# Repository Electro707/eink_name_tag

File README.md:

# E-Ink Name Tab Project, by Electro707

This project is for a E-Ink name-tag, meant to be the cooler replacement for a paper name-tag for event and shows.

## Directory

- `STM32CubeIDE`: The firmware created with STM32CubeIDE
- `PCB`: PCB Files made with KiCAD
- `PythonUploader`: A Python GUI and class to communicate with the e-ink tag, mainly to update the "frames"
- `CAD`: Mechanical enclosure made with FreeCAD

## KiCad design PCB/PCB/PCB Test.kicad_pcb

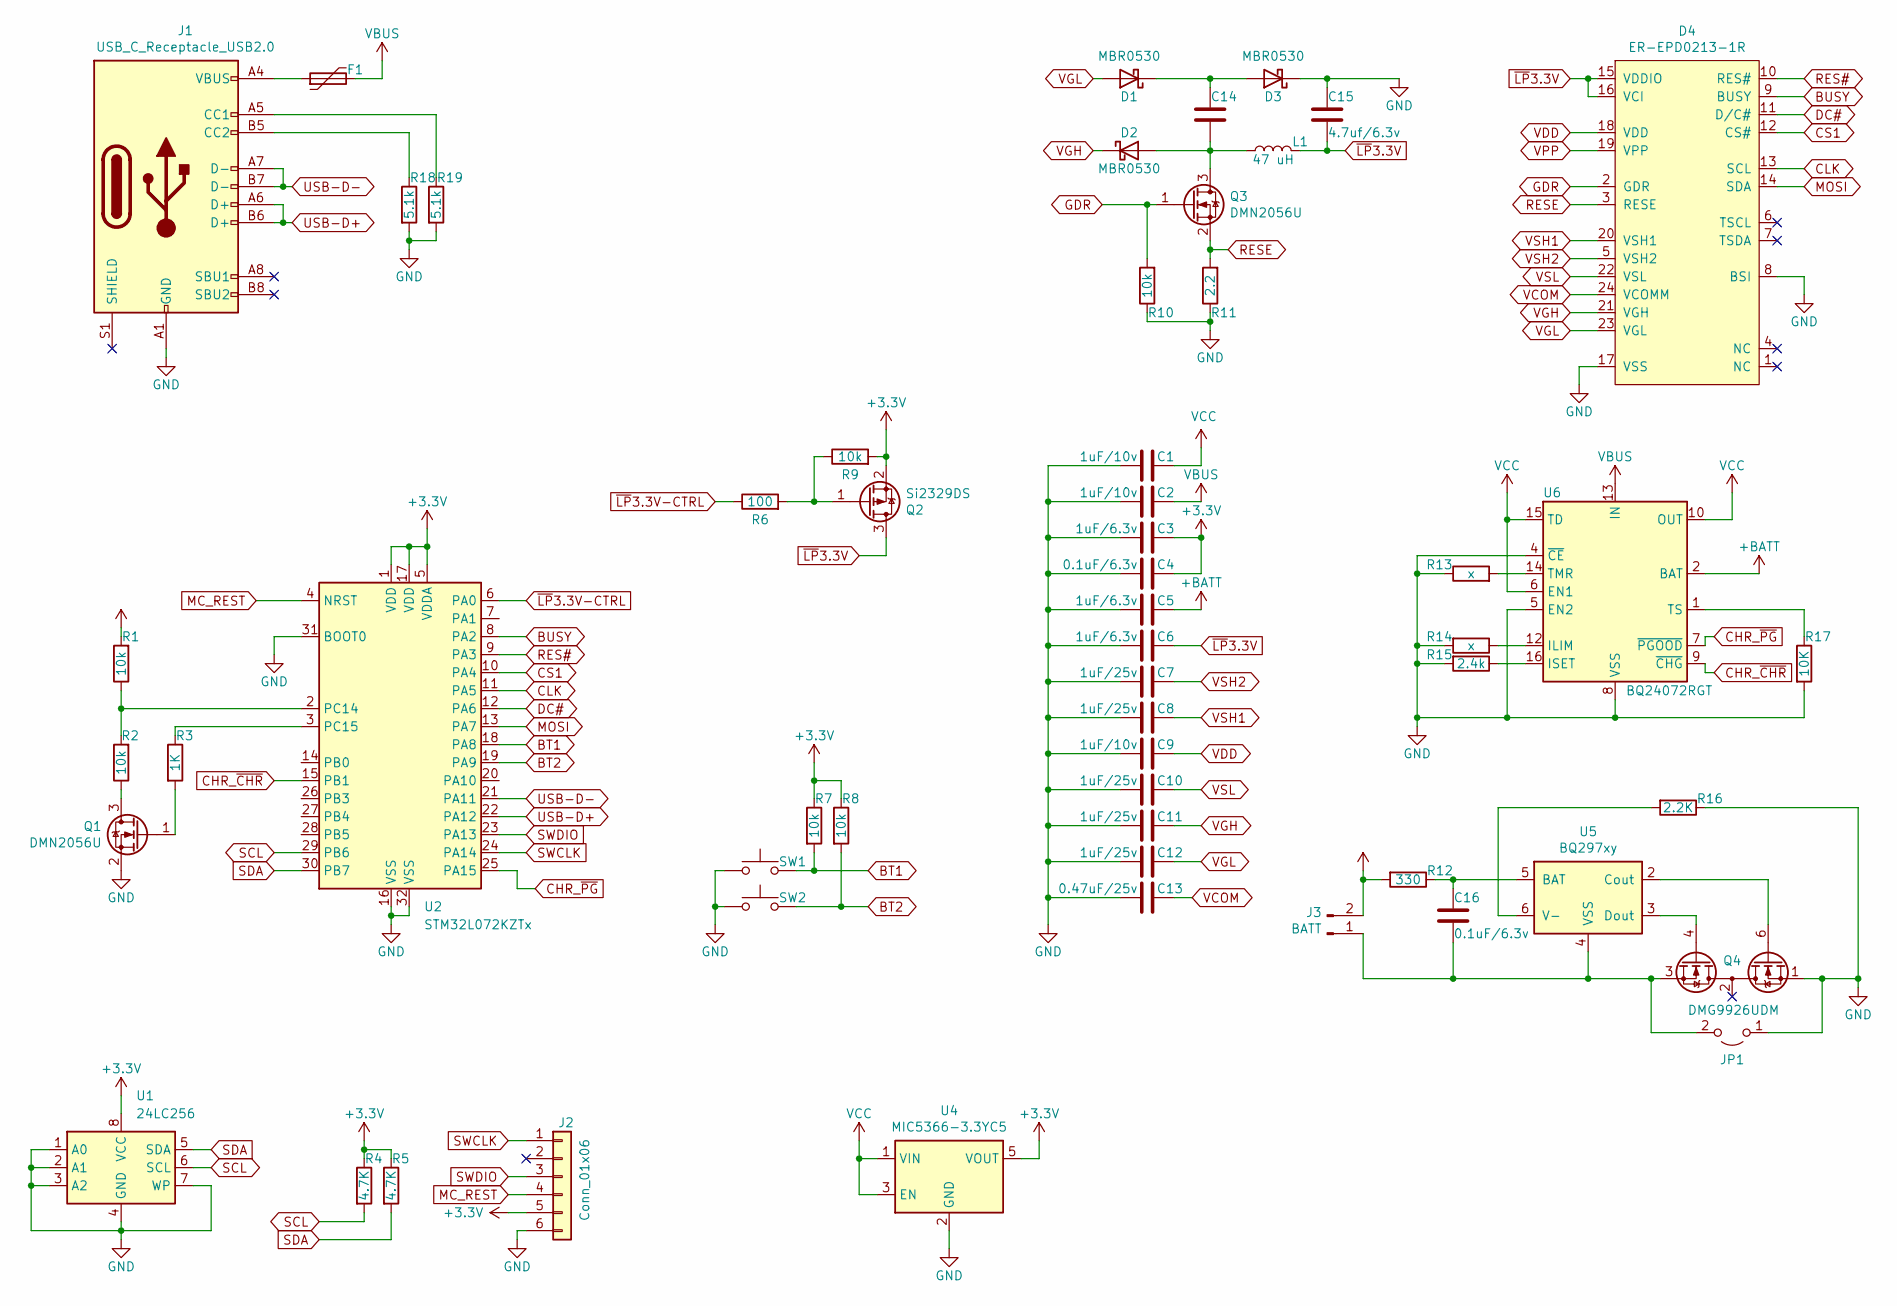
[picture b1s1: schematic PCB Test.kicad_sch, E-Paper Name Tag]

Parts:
C1, C2, C9: 1uF/10v; C_0805_2012Metric_Pad1.18x1.45mm_HandSolder
C3, C5, C6: 1uF/6.3v; C_0805_2012Metric_Pad1.18x1.45mm_HandSolder
C4, C16: 0.1uF/6.3v; C_0805_2012Metric_Pad1.18x1.45mm_HandSolder
C7, C8, C10, C11, C12: 1uF/25v; C_0805_2012Metric_Pad1.18x1.45mm_HandSolder
C13: 0.47uF/25v; C_0805_2012Metric_Pad1.18x1.45mm_HandSolder
C14: C_0805_2012Metric_Pad1.18x1.45mm_HandSolder
C15: 4.7uf/6.3v; C_0805_2012Metric_Pad1.18x1.45mm_HandSolder
D1, D2, D3: MBR0530; D_SOD-123
D4: ER-EPD0213-1R; TE_2-1734839-4_1x24-1MP_P0.5mm_Horizontal-EINK
F1: Polyfuse; Fuse_1210_3225Metric_Pad1.42x2.65mm_HandSolder
J1: USB_C_Receptacle_USB2.0; USB_C_Receptacle_GCT_USB4085
J2: Conn_01x06; Tag-Connect_TC2030-IDC-NL_2x03_P1.27mm_Vertical
J3: BATT; JST_PH_B2B-PH-SM4-TB_1x02-1MP_P2.00mm_Vertical
JP1: (no value)
L1: 47 uH; L_Taiyo-Yuden_NR-60xx_HandSoldering
Q1, Q3: DMN2056U; SOT-23
Q2: Si2329DS; SOT-23
Q4: DMG9926UDM; SOT-23-6
R1, R2, R7, R8, R9, R10: 10k; R_0805_2012Metric_Pad1.20x1.40mm_HandSolder
R3: 1K; R_0805_2012Metric_Pad1.20x1.40mm_HandSolder
R4, R5: 4.7K; R_0805_2012Metric_Pad1.20x1.40mm_HandSolder
R6: 100; R_0805_2012Metric_Pad1.20x1.40mm_HandSolder
R11: 2.2; R_0805_2012Metric_Pad1.20x1.40mm_HandSolder
R12: 330; R_0805_2012Metric_Pad1.20x1.40mm_HandSolder
R13, R14: x; R_0805_2012Metric_Pad1.20x1.40mm_HandSolder
R15: 2.4k; R_0805_2012Metric_Pad1.20x1.40mm_HandSolder
R16: 2.2K; R_0805_2012Metric_Pad1.20x1.40mm_HandSolder
R17: 10K; R_0805_2012Metric_Pad1.20x1.40mm_HandSolder
R18, R19: 5.1k; R_0805_2012Metric_Pad1.20x1.40mm_HandSolder
SW1, SW2: (no value)
U1: 24LC256; MSOP-8_3x3mm_P0.65mm
U2: STM32L072KZTx; LQFP-32_7x7mm_P0.8mm
U4: MIC5366-3.3YC5; SOT-353_SC-70-5
U5: BQ297xy; WSON-6_1.5x1.5mm_P0.5mm
U6: BQ24072RGT; VQFN-16-1EP_3x3mm_P0.5mm_EP1.6x1.6mm

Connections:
+3V3: C3.1, C4.1, J2.5, Q2.2 (S), R4.1, R5.1, R7.1, R8.1, R9.2, U1.8 (VCC), U2.1 (VDD), U2.5 (VDDA), U2.17 (VDD), U4.5 (VOUT)
BT1: R7.2, SW1.2, U2.18 (PA8)
BT2: R8.2, SW2.2, U2.19 (PA9)
BUSY: D4.9 (BUSY), U2.8 (PA2)
CHR_~CHR: U2.15 (PB1), U6.9 (~CHG)
CHR_~PG: U2.25 (PA15), U6.7 (~PGOOD)
CLK: D4.13 (SCL), U2.11 (PA5)
CS1: D4.12 (CS#), U2.10 (PA4)
DC#: D4.11 (D/C#), U2.12 (PA6)
GDR: D4.2 (GDR), Q3.1 (G), R10.2
GND: C1.2, C2.2, C3.2, C4.2, C5.2, C6.2, C7.2, C8.2, C9.2, C10.2, C11.2, C12.2, C13.2, C15.1, D3.1 (K), D4.8 (BSI), D4.17 (VSS), J1.A1 (GND), J1.A12 (GND), J1.B1 (GND), J1.B12 (GND), J2.6, JP1.1 (A), Q1.2 (S), Q4.1 (D1), R10.1, R11.1, R13.1, R14.2, R15.2, R16.1, R17.2, R18.2, R19.2, SW1.1, SW2.1, U1.1 (A0), U1.2 (A1), U1.3 (A2), U1.4 (GND), U1.7 (WP), U2.16 (VSS), U2.31 (BOOT0), U2.32 (VSS), U4.2 (GND), U6.4 (~CE), U6.5 (EN2), U6.8 (VSS), U6.17 (VSS)
MC_REST: J2.4, U2.4 (NRST)
MOSI: D4.14 (SDA), U2.13 (PA7)
unnamed: C14.1, D1.1 (K), D3.2 (A)
unnamed: C14.2, D2.2 (A), L1.1, Q3.3 (D)
unnamed: C16.1, R12.1, U5.5 (BAT)
unnamed: C16.2, J3.1, JP1.2 (B), Q4.3 (S2), U5.4 (VSS)
unnamed: F1.1, J1.A4 (VBUS), J1.A9 (VBUS), J1.B4 (VBUS), J1.B9 (VBUS)
unnamed: J1.A5 (CC1), R19.1
unnamed: J1.B5 (CC2), R18.1
unnamed: Q1.1 (G), R3.2
unnamed: Q1.3 (D), R2.1
unnamed: Q2.1 (G), R6.2, R9.1
unnamed: Q4.4 (G2), U5.3 (Dout)
unnamed: Q4.6 (G1), U5.2 (Cout)
unnamed: R13.2, U6.14 (TMR)
unnamed: R14.1, U6.12 (ILIM)
unnamed: R15.1, U6.16 (ISET)
unnamed: R16.2, U5.6 (V-)
unnamed: R17.1, U6.1 (TS)
unnamed: R1.1, R2.2, U2.2 (PC14)
unnamed: R3.1, U2.3 (PC15)
RES#: D4.10 (RES#), U2.9 (PA3)
RESE: D4.3 (RESE), Q3.2 (S), R11.2
SCL: R4.2, U1.6 (SCL), U2.29 (PB6)
SDA: R5.2, U1.5 (SDA), U2.30 (PB7)
SWCLK: J2.1, U2.24 (PA14)
SWDIO: J2.3, U2.23 (PA13)
USB-D+: J1.A6 (D+), J1.B6 (D+), U2.22 (PA12)
USB-D-: J1.A7 (D-), J1.B7 (D-), U2.21 (PA11)
VBUS: C2.1, F1.2, U6.13 (IN)
VCC: C1.1, U4.1 (VIN), U4.3 (EN), U6.6 (EN1), U6.10 (OUT), U6.11 (OUT), U6.15 (TD)
VCOM: C13.1, D4.24 (VCOMM)
VDD: C9.1, D4.18 (VDD)
VGH: C11.1, D2.1 (K), D4.21 (VGH)
VGL: C12.1, D1.2 (A), D4.23 (VGL)
VPP: D4.19 (VPP)
VSH1: C8.1, D4.20 (VSH1)
VSH2: C7.1, D4.5 (VSH2)
VSL: C10.1, D4.22 (VSL)
~LP3.3V: C6.1, C15.2, D4.15 (VDDIO), D4.16 (VCI), L1.2, Q2.3 (D)
~LP3.3V-CTRL: R6.1, U2.6 (PA0)

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
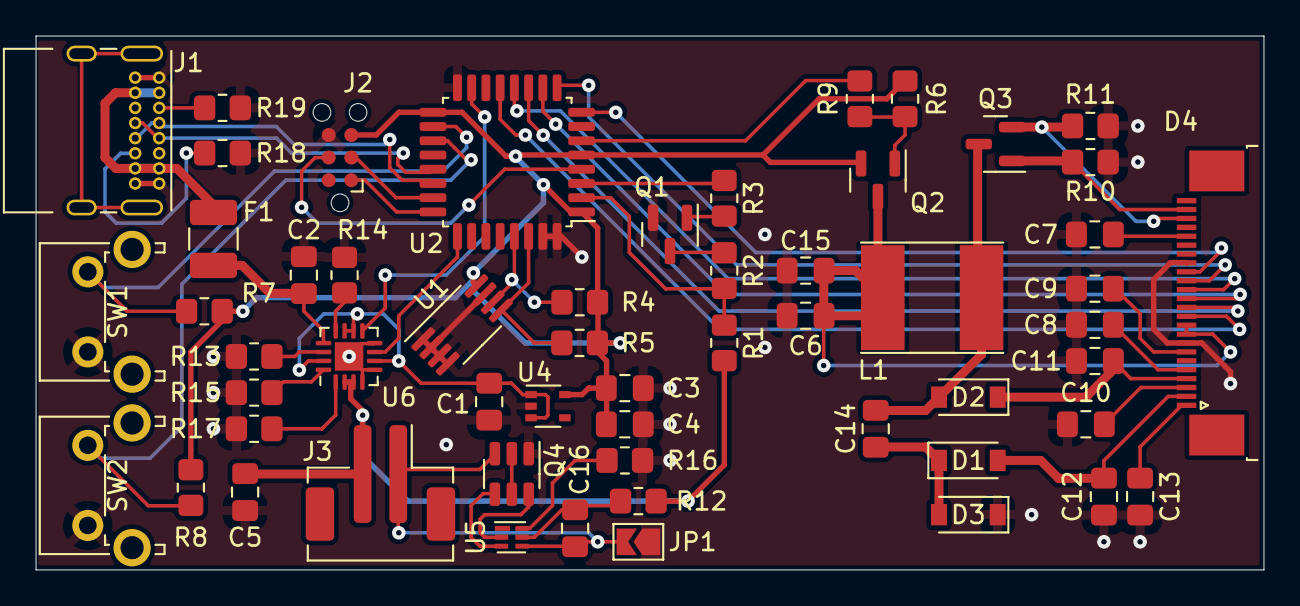
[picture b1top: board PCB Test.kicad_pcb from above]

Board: 2 copper layers, 69.0 x 30.0 mm, 56 parts (0 on the bottom side), 52 nets.

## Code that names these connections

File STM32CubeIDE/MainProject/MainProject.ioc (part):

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Mcu.Name=STM32L072K(B-Z)Tx
Mcu.Package=LQFP32
Mcu.UserName=STM32L072KZTx
PA0.GPIOParameters=GPIO_Label
PA0.GPIO_Label=POWER_SWITCH
PA0.Signal=GPIO_Output
PA11.Mode=Device
PA11.Signal=USB_DM
PA12.Mode=Device
PA12.Signal=USB_DP
PA13.Mode=Serial_Wire
PA13.Signal=SYS_SWDIO
PA14.Mode=Serial_Wire
PA14.Signal=SYS_SWCLK
PA2.GPIOParameters=GPIO_Label
PA2.GPIO_Label=EPAPER_BUSY
PA2.Signal=GPIO_Input
PA3.GPIOParameters=GPIO_Speed,GPIO_Label
PA3.GPIO_Label=EPAPER_RST
PA3.GPIO_Speed=GPIO_SPEED_FREQ_HIGH
PA3.Signal=GPIO_Output
PA4.GPIOParameters=GPIO_Speed,GPIO_Label
PA4.GPIO_Label=EPAPER_CS
PA4.GPIO_Speed=GPIO_SPEED_FREQ_VERY_HIGH
PA4.Signal=GPIO_Output
PA5.Mode=Simplex_Bidirectional_Master
PA5.Signal=SPI1_SCK
PA6.GPIOParameters=GPIO_Speed,GPIO_Label
PA6.GPIO_Label=EPAPER_DC
PA6.GPIO_Speed=GPIO_SPEED_FREQ_VERY_HIGH
PA6.Signal=GPIO_Output
PA7.Mode=Simplex_Bidirectional_Master
PA7.Signal=SPI1_MOSI
PA8.GPIOParameters=GPIO_Label
PA8.GPIO_Label=BUTTON1
PA8.Signal=GPXTI8
PA9.GPIOParameters=GPIO_Label
PA9.GPIO_Label=BUTTON2
PA9.Signal=GPXTI9
PB6.Mode=I2C
PB6.Signal=I2C1_SCL
PB7.Mode=I2C
PB7.Signal=I2C1_SDA
RCC.SYSCLKFreq_VALUE=32000000
RCC.SYSCLKSource=RCC_SYSCLKSOURCE_PLLCLK
board=custom

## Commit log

2021-07-15 Initial Release
2021-08-23 Added more code docs. Started switching flags to ENUMs
2021-08-24 Added option to set max frames. Lots of Python GUI refractoring
2021-08-25 Removed older schematic file
2022-04-17 Updated schematic to Rev C
2022-04-17 Updated firmware for RevC of the PCB
2022-04-18 Added CAD models. Updated Python scipt. Added shematic
2022-09-12 Updated CAD model to include a lanyard slot. Changes with code described below:
    Added a user settings allocation in the EEPROM, for example for the number of available frames
    Added more comments to code
    Fixed bug where pressing the button while the display is updated will cause another updated. Also serves as a cheap "debouncing"
2022-10-02 Added new picture
2022-10-02 Changed order of README.md images
